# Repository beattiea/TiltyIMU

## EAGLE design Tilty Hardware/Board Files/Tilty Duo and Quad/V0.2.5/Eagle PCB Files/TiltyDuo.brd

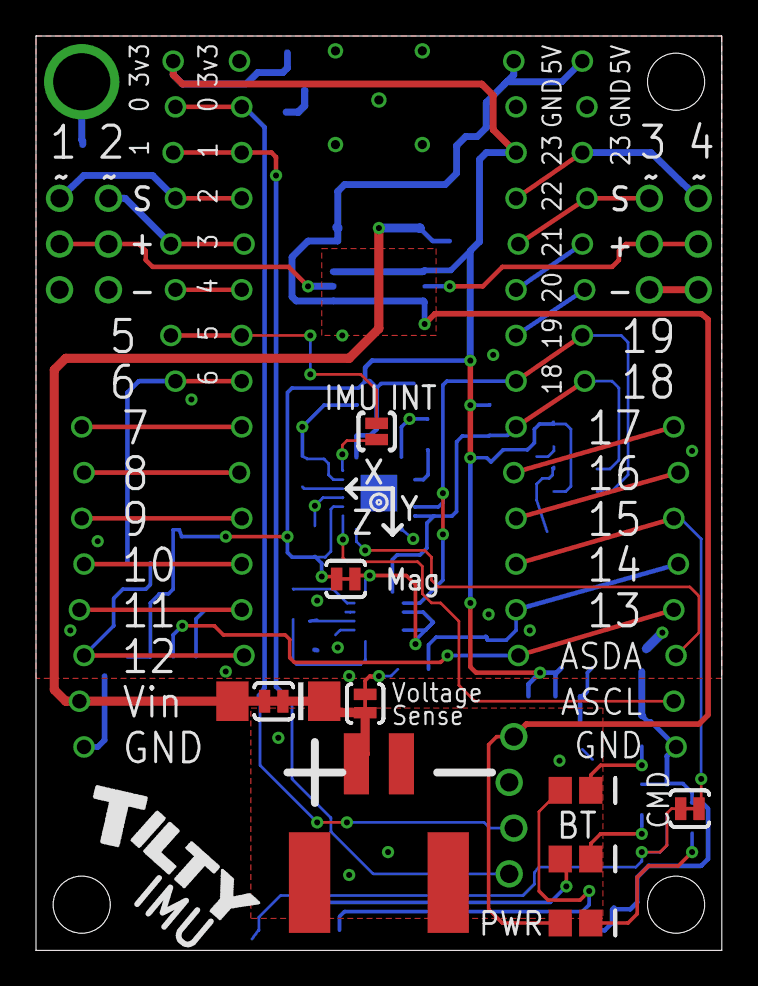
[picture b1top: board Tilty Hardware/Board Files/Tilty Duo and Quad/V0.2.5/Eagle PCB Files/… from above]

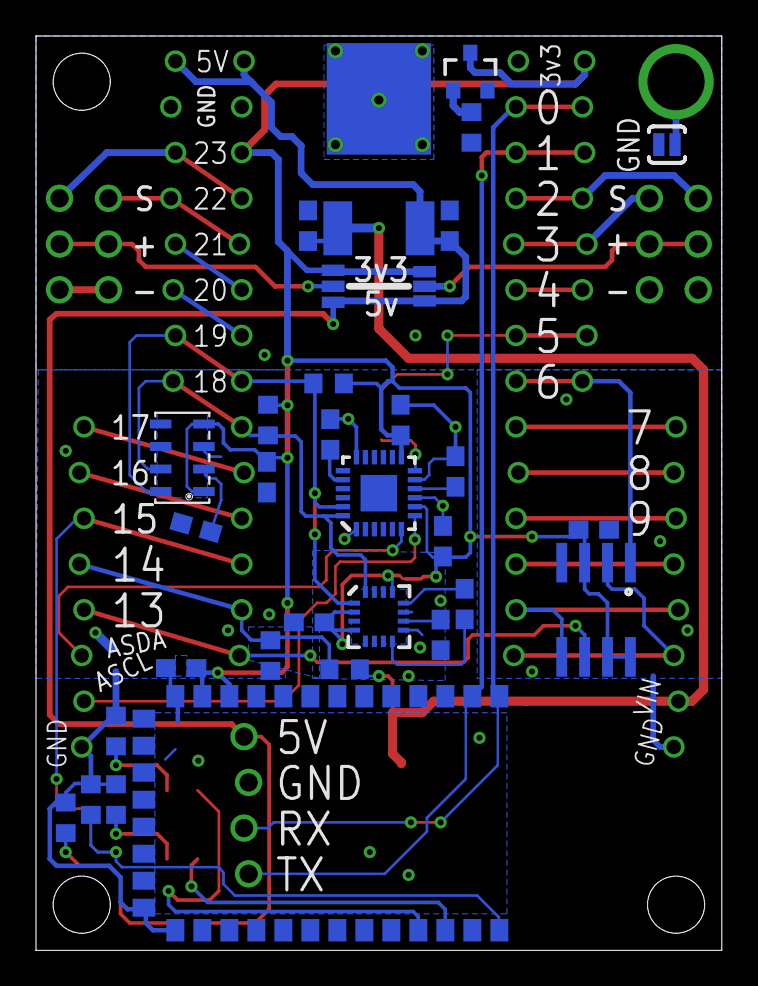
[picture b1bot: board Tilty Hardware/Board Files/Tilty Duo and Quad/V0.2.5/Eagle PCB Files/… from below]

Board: 2 copper layers, 38.1 x 50.8 mm, 50 parts (32 on the bottom side), 48 nets.

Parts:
C1, C2, C4, C6, C9, C10, C11, C12, C13: 0.1uF; C0603
C3: 2.2nF; C0603
C5, C8: 4.7uF; C0603
C7: 0.22uF; C0603
D1: RED; LED-0805
D2: GREEN; LED-0805
D3: YELLOW; LED-0805
D5: SOT23-3
D6: DO214AA
JP1, JP2, JP3, JP4: 8-PIN_HEADER; 8-PIN_RECEPTACLE_LOCK_NO-SS
JP5: 2-POS_SMD_TERM_BLOCK; 2-POS_SMD_TERMINAL_BLOCK
JP6, JP7: 2X03_NO_SS_LOCK
JP9: 1X04_NO_SS_LOCKING
MPU_INT: SOLDERJUMPERNO; SJ_2S-NO
R1, R2: 4.7K; R0603
R3: 180; R0603
R4, R8: 68; R0603
R5: 10k; R0603
R6: 680; R0603
R7: 10K; R0603
R9: R0603
SJ1: SOLDERJUMPERNO; SJ_2S-NO
SJ2: SJ_3_PASTE1&2
SJ3: SJ_3
SJ4, SJ5, SJ6, SJ7: SOLDERJUMPERTRACE; SJ_2S-TRACE
U1: TEENSY_3.0_OUTER-PINS28-DIP_SOCKET; 28-DIP
U2: MPU-6050; QFN-24
U3: LM2931; TO263
U4: SPI_FLASH-X25XXSMD; SO08
U5: HC-09_BREAKOUT
U6: HMC5883LSMD; 16LPCC
U7: MPL3115A2LGA8; LGA8

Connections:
5V: C5.1, D2.1, JP4.P$1, JP9.4, SJ2.1, SJ3.1, U1.P$15, U3.P$3
AUXCL: JP3.P$7, U2.7
AUXDA: JP3.P$6, U2.6
BATT_SENSE: JP3.P$4, R5.2, R6.2, U1.P$27
BT_CMD: JP3.P$3, SJ5.1, U1.P$26
CMD: R7.2, SJ5.2, U5.P$34
CS: JP1.P$1, U1.P$8, U4.1
GND: C1.2, C2.1, C3.2, C4.2, C5.2, C6.2, C8.2, C9.2, C10.2, C11.1, C12.1, C13.1, JP2.P$1, JP3.P$8, JP4.P$2, JP5.P$4, JP6.1, JP6.2, JP7.1, JP7.2, JP9.3, R3.1, R4.2, R6.1, R7.1, R8.1, R9.1, SJ1.2, U1.P$1, U1.P$16, U2.1, U2.9, U2.11, U2.18, U3.P$1, U4.4, U5.P$13, U5.P$21, U5.P$22, U6.9, U6.11, U7.3
I/O1: JP1.P$5, JP6.6, U1.P$4
I/O2: JP1.P$4, JP6.5, U1.P$5
I/O3: JP4.P$3, JP7.5, U1.P$18
I/O4: JP4.P$4, JP7.6, U1.P$19
MISO: JP2.P$3, U1.P$14, U4.2
MOSI: JP2.P$4, U1.P$13, U4.5
MPU_INT: JP1.P$2, MPU_INT.1, U1.P$7
unnamed: C1.1, U2.10
unnamed: C3.1, U2.20
unnamed: D1.2, R3.2
unnamed: C7.1, U6.8
unnamed: C7.2, U6.12
unnamed: JP1.P$3, U1.P$6
unnamed: JP2.P$5, U1.P$12
unnamed: R5.1, SJ4.2
unnamed: JP3.P$1, U1.P$24
unnamed: C8.1, U6.10
unnamed: JP2.P$6, U1.P$11
unnamed: D2.2, R4.1
unnamed: D1.1, U5.P$31
unnamed: MPU_INT.2, U2.12
unnamed: C6.1, SJ7.2, U6.2, U6.4, U6.13
unnamed: JP4.P$5, U1.P$20
unnamed: JP4.P$6, U1.P$21
unnamed: C10.1, U7.2
unnamed: D5.1, R9.2
unnamed: JP3.P$2, U1.P$25
unnamed: D3.2, R8.2
POW_I/O1: JP6.3, JP6.4, SJ2.2
POW_I/O2: JP7.3, JP7.4, SJ3.2
RX1: JP1.P$7, JP9.2, U1.P$2, U5.P$1
RX3: JP2.P$8, U1.P$9
SCK: JP3.P$5, U1.P$28, U4.6
SCL: JP4.P$7, R1.1, U1.P$22, U2.23, U6.1, U7.8
SDA: JP4.P$8, R2.1, U1.P$23, U2.24, U6.16, U7.7
TEENSY_3V3: C2.2, C9.1, C11.2, C12.2, C13.2, D5.3, JP1.P$8, R1.2, R2.2, SJ2.3, SJ3.3, SJ7.1, U1.P$17, U2.8, U2.13, U4.3, U4.7, U4.8, U5.P$11, U5.P$12, U7.1, U7.4
TX1: JP1.P$6, JP9.1, U1.P$3, U5.P$2
TX3: JP2.P$7, U1.P$10
VBATT: C4.1, D6.A, D6.C, JP2.P$2, JP5.P$3, SJ4.1, SJ6.1, SJ6.2, U3.P$2
YEL_LED: D3.1, U5.P$32

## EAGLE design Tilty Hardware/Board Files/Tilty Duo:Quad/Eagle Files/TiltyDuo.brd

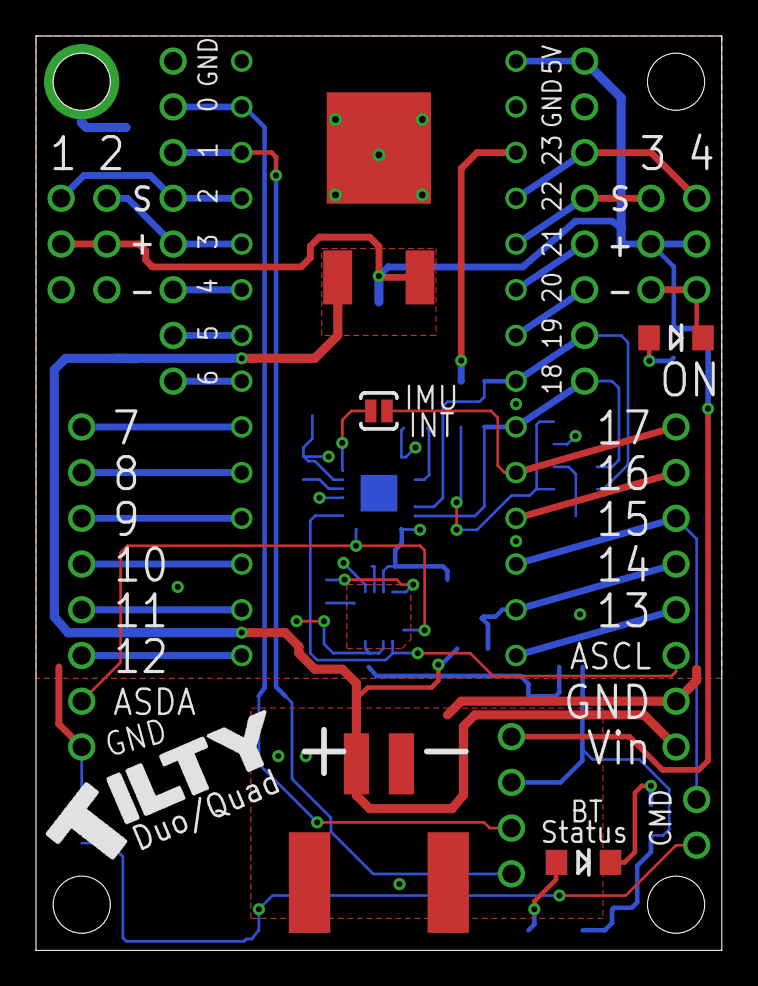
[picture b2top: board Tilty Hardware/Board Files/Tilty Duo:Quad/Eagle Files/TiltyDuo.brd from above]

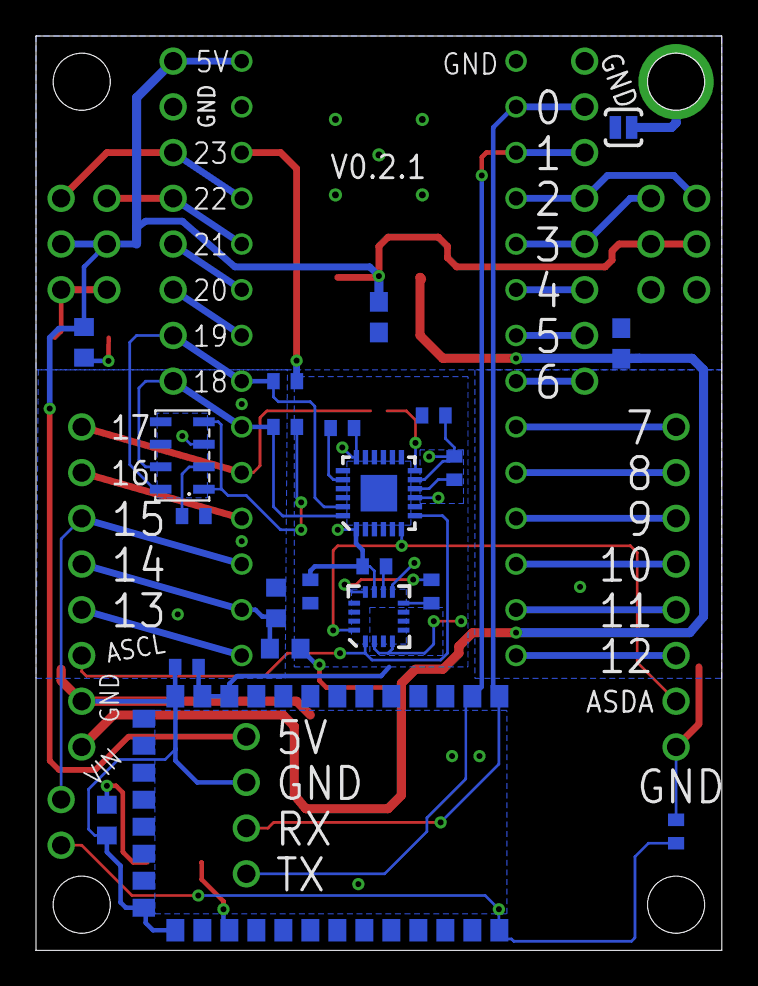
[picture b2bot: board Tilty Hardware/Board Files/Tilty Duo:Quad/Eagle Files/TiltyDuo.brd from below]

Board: 2 copper layers, 38.1 x 50.8 mm, 36 parts (22 on the bottom side), 41 nets.

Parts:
C1, C2, C6, C9, C10: 0.1uF; C0402
C3: 2.2nF; C0402
C4: 0.1uF; C0603
C5: 1uF; C0603
C7: 0.22uF; C0402
C8: 4.7uF; C0402
D1: GREEN; LED-1206_NO_SS
D2: RED; LED-1206_NO_SS
JP1, JP2, JP5, JP6: 1X08_NO_SS
JP3, JP7: 2X03_NO_SS
JP4: 2-POS_SMD_TERM_BLOCK; 2-POS_SMD_TERMINAL_BLOCK
JP8: 1X02_NO_SS
JP9: 1X04
MPU_INT: SOLDERJUMPERNO; SJ_2S-NO
R1, R2, R7: 4.7K; R0402
R3: 470; R0603
R4: 180; R0603
R5: 10k; R0603
R6: 680; R0603
SJ1: SOLDERJUMPERNO; SJ_2S-NO
U1: TEENSY_3.0_OUTER-PINS28-DIP_SOCKET; 28-DIP
U2: HC-09_BREAKOUT
U3: MPL3115A2LGA8; LGA8
U4: LM2931; TO263
U5: MPU-6050; QFN-24
U6: HMC5883LSMD; 16LPCC

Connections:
5V: C5.1, JP3.3, JP3.4, JP5.8, JP7.3, JP7.4, JP9.4, R4.1, U1.P$15, U4.P$3
AUXCL: JP6.3, U5.7, U6.1
AUXDA: JP2.2, U5.6, U6.16
BATT_SENSE: JP6.5, R5.2, R6.2, U1.P$27
BT_CMD: JP6.6, JP8.1, U1.P$26
CMD: JP8.2, R7.2, U2.P$34
GND: C1.2, C2.1, C3.2, C4.2, C5.2, C6.2, C8.2, C9.2, C10.2, D2.C, JP1.8, JP2.1, JP3.1, JP3.2, JP4.P$4, JP5.7, JP6.2, JP7.1, JP7.2, JP9.3, R3.1, R6.1, R7.1, SJ1.2, U1.P$1, U2.P$13, U2.P$21, U2.P$22, U3.3, U4.P$1, U5.1, U5.9, U5.11, U5.18, U6.9, U6.11
I/O1: JP1.5, JP3.6, U1.P$4
I/O2: JP1.4, JP3.5, U1.P$5
I/O3: JP5.6, JP7.5, U1.P$18
I/O4: JP5.5, JP7.6, U1.P$19
LED: D1.A, U2.P$24
MPU_INT: JP6.8, MPU_INT.1, U1.P$24
unnamed: C1.1, U5.10
unnamed: C3.1, U5.20
unnamed: D1.C, R3.2
unnamed: C7.1, U6.8
unnamed: C7.2, U6.12
unnamed: JP1.3, U1.P$6
unnamed: JP1.2, U1.P$7
unnamed: JP1.1, U1.P$8
unnamed: JP6.4, U1.P$28
unnamed: C8.1, U6.10
unnamed: JP2.6, U1.P$11
unnamed: JP2.5, U1.P$12
unnamed: JP2.4, U1.P$13
unnamed: JP2.3, U1.P$14
unnamed: MPU_INT.2, U5.12
unnamed: D2.A, R4.2
unnamed: JP5.4, U1.P$20
unnamed: JP5.3, U1.P$21
unnamed: C10.1, U3.2
unnamed: JP6.7, U1.P$25
RX1: JP1.7, JP9.2, U1.P$2, U2.P$1
RX3: JP2.8, U1.P$9
SCL: JP5.2, R1.1, U1.P$22, U3.8, U5.23
SDA: JP5.1, R2.1, U1.P$23, U3.7, U5.24
TEENSY_3V3: C2.2, C6.1, C9.1, R1.2, R2.2, U1.P$17, U2.P$11, U2.P$12, U3.1, U3.4, U5.8, U5.13, U6.2, U6.4, U6.13
TX1: JP1.6, JP9.1, U1.P$3, U2.P$2
TX3: JP2.7, U1.P$10
VBATT: C4.1, JP4.P$3, JP6.1, R5.1, U4.P$2

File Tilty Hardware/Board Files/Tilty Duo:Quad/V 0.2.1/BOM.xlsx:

Part | Package | Name | Quantity | Supplier 1 | Part # 1 | Cost per 1 | Cost per 10 | Cost per 25 | Cost per 50 | Cost per 100 | Supplier 2 | Part # 2 | Cost | Quantity |  | Cost/board for 50 boards
Teensy DIP Socket | DIP | U1 | 1 | Digikey | AE10004-ND | 0.42 | 0.39900000000000002 | 0.34200000000000003 | 0.2908 | 0.27929999999999999 | Avnet | 1-390262-2 | 0.22320000000000001 | 50 |  | 0.2908
Bluetooth Module | Surface mount | U2 | 1 | Aliexpress |  | 5.99 | 5.99 | 4.12 | 4.12 | 4.0999999999999996 | eBay |  |  |  |  | 4.12
Voltage Regulator | Dpak | U4 | 1 | Digikey | LM2931ADT-5.0GOS-ND | 0.78 | 0.78 | 0.60599999999999998 | 0.60599999999999998 | 0.52790000000000004 | Avnet | LM2931DT-5.0G | 0.375 | 1 |  | 0.60599999999999998
MPU-6050 IMU | QFN | U5 | 1 | Aliexpress |  | 4 | 2.5 | 2.5 | 2.5 | 2.5 | eBay |  |  |  |  | 2.5
1x8 Female headers | DIP | JP1, JP2, JP5, JP6 | 4 | Aliexpress |  | 1.43 | 1.2989999999999999 | 1.2989999999999999 | 1.1659999999999999 | 0.16 | Digikey | 535541-6 |  |  |  | 4.6639999999999997
2x40 Male Headers (cut from strip) | DIP | JP3, JP7, JP8 | 0.2 | Aliexpress |  | 1.03 | 0.91800000000000004 | 0.91800000000000004 | 0.91800000000000004 | 0.12 | Digikey | S2012EC-40-ND |  |  |  | 0.18360000000000001
Power Terminal | Surface mount | JP4 | 1 | Digikey | 277-2337-1-ND | 0.61 | 0.56399999999999995 | 0.56399999999999995 | 0.54059999999999997 | 0.51700000000000002 |  |  |  |  |  | 0.54059999999999997
Green LED | 1206 | D1 | 1 | Digikey | L71504CT-ND | 0.5 | 0.38900000000000001 | 0.31680000000000003 | 0.31680000000000003 | 0.252 | Check Avne for alternative |  |  |  |  | 0.31680000000000003
Red LED | 1206 | D2 | 1 | Digikey | 516-2825-1-ND | 0.56000000000000005 | 0.43 | 0.36 | 0.36 | 0.31 | Check Avne for alternative |  |  |  |  | 0.36
4.7K Ω Resistor | 0402 | R1, R2, R7 | 3 | Digikey | P4.7KJCT-ND | 0.1 | 0.1 | 0.1 | 1.72E-2 | 1.3100000000000001E-2 | Avnet | ERJ-2GEJ472X | 2E-3 | 10000 |  | 5.16E-2
470 Ω Resistor | 0603 | R3 | 1 | Digikey | RMCF0603JT470RCT-ND | 0.02 | 1.7000000000000001E-2 | 1.7000000000000001E-2 | 9.1999999999999998E-3 | 7.0000000000000001E-3 | Avnet | RMCF0603JT470R | 1.6000000000000001E-3 | 5000 |  | 9.1999999999999998E-3
180 Ω Resistor | 0603 | R4 | 1 | Digikey | RNCP0603FTD180RCT-ND | 0.05 | 3.7999999999999999E-2 | 3.7999999999999999E-2 | 2.0799999999999999E-2 | 1.5800000000000002E-2 | Avnet | ERJ-3GEYJ181V | 1.1000000000000001E-3 | 5000 |  | 2.0799999999999999E-2
10K Ω Resistor | 0603 | R5 | 1 | Digikey | RMCF0603JT10K0CT-ND | 0.02 | 1.7000000000000001E-2 | 1.7000000000000001E-2 | 9.1999999999999998E-3 | 7.0000000000000001E-3 | Avnet | RMCF0603JT10K0 | 1.6000000000000001E-3 | 5000 |  | 9.1999999999999998E-3
680 Ω Resistor | 0603 | R6 | 1 | Digikey | RMCF0603JT680R | 0.02 | 1.7000000000000001E-2 | 1.7000000000000001E-2 | 9.1999999999999998E-3 | 7.0000000000000001E-3 | Avnet | RMCF0603JT680R | 1.6000000000000001E-3 | 5000 |  | 9.1999999999999998E-3
0.1 µF Capacitor | 0402 | C1, C2, C9 | 3 | Digikey | C1005X5R1A104K050BA | 0.1 | 2.5000000000000001E-2 | 2.5000000000000001E-2 | 2.5000000000000001E-2 | 1.1599999999999999E-2 | Avnet | C1005X5R1A104K050BA | 3.7000000000000002E-3 | 10000 |  | 7.5000000000000011E-2
2.2 nF Capacitor | 0402 | C3 | 1 | Digikey | C1005X7R1H222K050BA | 0.1 | 2.4E-2 | 2.4E-2 | 2.4E-2 | 1.0999999999999999E-2 | Avnet | C1005X7R1H222K050BA | 3.5000000000000001E-3 | 10000 |  | 2.4E-2
0.1 µF Capacitor | 0603 | C4 | 1 | Digikey | C1608Y5V1H104Z | 0.1 | 2.8000000000000001E-2 | 2.8000000000000001E-2 | 2.8000000000000001E-2 | 1.26E-2 | Avnet | C1608Y5V1H104Z | 3.8999999999999998E-3 | 4000 |  | 2.8000000000000001E-2
1 µF Capacitor | 0603 | C5 | 1 | Digikey | C1608X5R1A105K080AC | 0.1 | 6.2E-2 | 6.2E-2 | 6.2E-2 | 2.86E-2 | Avnet | C1608X5R1A105K080AC | 9.1999999999999998E-3 | 4000 |  | 6.2E-2
 |  |  |  |  |  |  |  |  |  |  |  |  |  |  |  | 13.870799999999997

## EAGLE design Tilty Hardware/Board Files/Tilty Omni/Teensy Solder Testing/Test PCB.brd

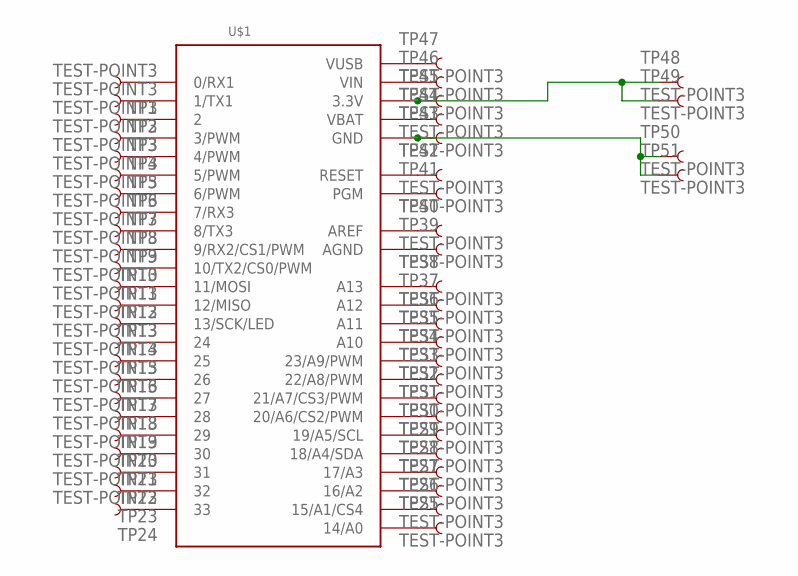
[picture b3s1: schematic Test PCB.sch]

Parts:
TP1, TP2, TP3, TP4, TP5, TP6, TP7, TP8, TP9, TP10, TP11, TP12, TP13, TP14, TP15, TP16, TP17, TP18, TP19, TP20, TP21, TP22, TP23, TP24, TP25, TP26, TP27, TP28, TP29, TP30, TP31, TP32, TP33, TP34, TP35, TP36, TP37, TP38, TP39, TP40, TP41, TP42, TP43, TP44, TP45, TP46, TP47, TP48, TP49, TP50, TP51: TEST-POINT3; PAD.03X.03
U$1: TEENSY_3.0_ALLPINSTEENSY_3.0_ALLPINS-SMD; TEENSY_3.0_ALLPINS-SMD

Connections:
unnamed: TP1.P$1, U$1.0 (0/RX1)
unnamed: TP2.P$1, U$1.1 (1/TX1)
unnamed: TP3.P$1, U$1.2
unnamed: TP4.P$1, U$1.3 (3/PWM)
unnamed: TP5.P$1, U$1.4 (4/PWM)
unnamed: TP6.P$1, U$1.5 (5/PWM)
unnamed: TP7.P$1, U$1.6 (6/PWM)
unnamed: TP8.P$1, U$1.7 (7/RX3)
unnamed: TP9.P$1, U$1.8 (8/TX3)
unnamed: TP10.P$1, U$1.9 (9/RX2/CS1/PWM)
unnamed: TP11.P$1, U$1.10 (10/TX2/CS0/PWM)
unnamed: TP12.P$1, U$1.11 (11/MOSI)
unnamed: TP13.P$1, U$1.12 (12/MISO)
unnamed: TP14.P$1, U$1.13 (13/SCK/LED)
unnamed: TP15.P$1, U$1.24
unnamed: TP16.P$1, U$1.25
unnamed: TP17.P$1, U$1.26
unnamed: TP18.P$1, U$1.27
unnamed: TP19.P$1, U$1.28
unnamed: TP20.P$1, U$1.29
unnamed: TP21.P$1, U$1.30
unnamed: TP22.P$1, U$1.31
unnamed: TP23.P$1, U$1.32
unnamed: TP24.P$1, U$1.33
unnamed: TP25.P$1, U$1.14/A0
unnamed: TP26.P$1, U$1.15/A1 (15/A1/CS4)
unnamed: TP27.P$1, U$1.16/A2
unnamed: TP28.P$1, U$1.17/A3
unnamed: TP29.P$1, U$1.18/A4 (18/A4/SDA)
unnamed: TP30.P$1, U$1.19/A5 (19/A5/SCL)
unnamed: TP31.P$1, U$1.20/A6 (20/A6/CS2/PWM)
unnamed: TP32.P$1, U$1.21/A7 (21/A7/CS3/PWM)
unnamed: TP33.P$1, U$1.22/A8 (22/A8/PWM)
unnamed: TP34.P$1, U$1.23/A9 (23/A9/PWM)
unnamed: TP35.P$1, U$1.A10
unnamed: TP36.P$1, U$1.A11
unnamed: TP37.P$1, U$1.A12
unnamed: TP38.P$1, U$1.A13
unnamed: TP39.P$1, U$1.AGND
unnamed: TP40.P$1, U$1.AREF
unnamed: TP41.P$1, U$1.PGM
unnamed: TP42.P$1, U$1.RESET
unnamed: TP44.P$1, U$1.VBAT
unnamed: TP43.P$1, TP50.P$1, TP51.P$1, U$1.GND, U$1.GND1 (GND), U$1.GND2 (GND)
unnamed: TP46.P$1, U$1.VIN
unnamed: TP47.P$1, U$1.VUSB
unnamed: TP45.P$1, TP48.P$1, TP49.P$1, U$1.3.3V, U$1.3.3V1 (3.3V), U$1.3.3V2 (3.3V)

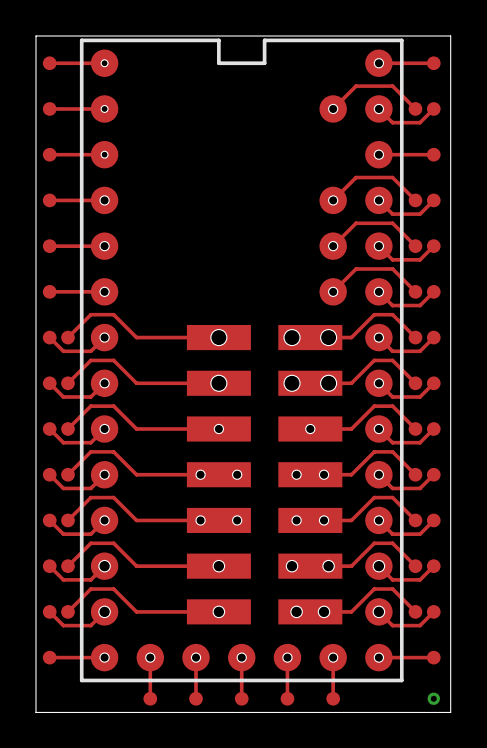
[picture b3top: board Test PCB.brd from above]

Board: 2 copper layers, 23.0 x 37.6 mm, 52 parts (0 on the bottom side), 47 nets.

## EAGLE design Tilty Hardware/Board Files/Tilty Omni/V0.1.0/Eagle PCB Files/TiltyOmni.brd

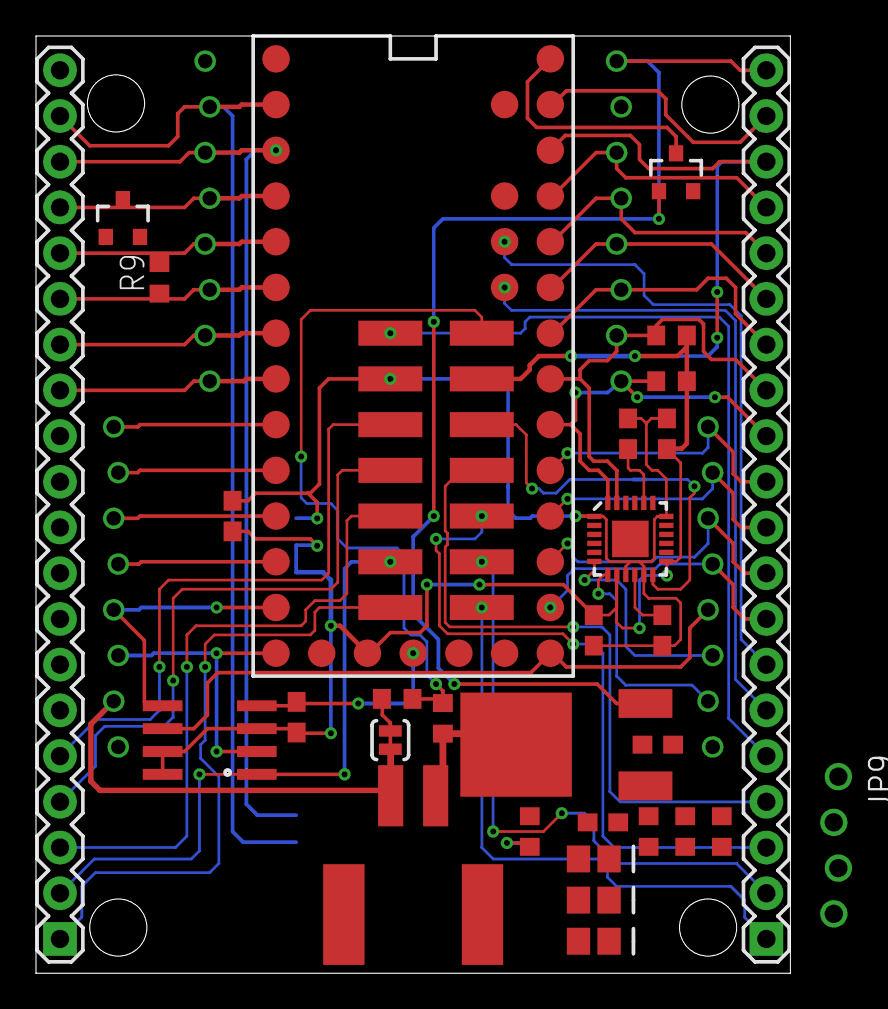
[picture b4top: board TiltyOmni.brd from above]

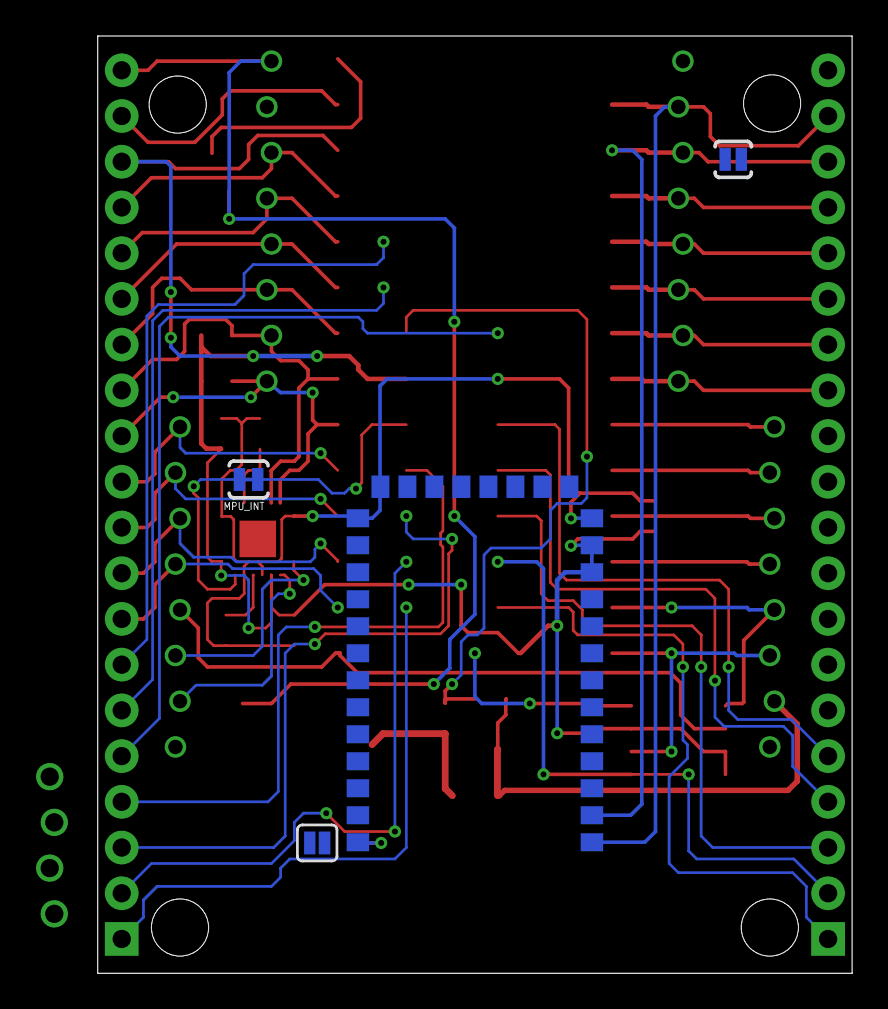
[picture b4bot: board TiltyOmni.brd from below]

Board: 2 copper layers, 41.9 x 52.1 mm, 39 parts (4 on the bottom side), 57 nets.

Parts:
C1, C2, C4, C9, C11, C13: 0.1uF; C0603
C3: 2.2nF; C0603
C5: 4.7uF; C0603
D1: RED; LED-0805
D2: GREEN; LED-0805
D3: YELLOW; LED-0805
D4, D5: SOT23-3
JP1, JP2, JP3, JP4: 8-PIN_HEADER; 8-PIN_RECEPTACLE_LOCK_NO-SS
JP5: 2-POS_SMD_TERM_BLOCK; 2-POS_SMD_TERMINAL_BLOCK
JP6, JP7: M20; 1X20
JP9: 1X04_NO_SS_LOCKING
MPU_INT: SOLDERJUMPERTRACE; SJ_2S-TRACE
R1, R2: 4.7K; R0603
R3: 180; R0603
R4, R8: 68; R0603
R5: 10k; R0603
R6: 680; R0603
R7: 10K; R0603
R9: R0603
SJ1: SOLDERJUMPERNO; SJ_2S-NO
SJ4: SOLDERJUMPERTRACE; SJ_2S-TRACE
SJ5: SJ_2S
U1: TEENSY_3.0_ALLPINSTEENSY_3.0_ALLPINS-SMD; TEENSY_3.0_ALLPINS-SMD
U2: HC-09_BREAKOUT
U4: LM2931; TO263
U5: MPU-6050; QFN-24
U7: SPI_FLASH-X25XXSMD; SO08

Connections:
3V_SCL: JP4.P$7, JP7.13, R1.1, U1.19/A5, U5.23
3V_SDA: JP4.P$8, JP7.12, R2.1, U1.18/A4, U5.24
4/PWM: JP1.P$6, JP6.15, U1.4
5/PWM: JP1.P$7, JP6.14, U1.5
5V_SCL: JP3.P$2, JP7.10, U1.16/A2
5V_SDA: JP3.P$1, JP7.11, U1.17/A3
6/PWM: JP1.P$8, JP6.13, U1.6
7/RX3: JP2.P$1, JP6.12, U1.7
8/TX3: JP2.P$2, JP6.11, U1.8
9/RX2: JP2.P$3, JP6.10, U1.9
10/TX2: JP2.P$4, JP6.9, U1.10
14/A0: JP3.P$4, JP7.8, U1.14/A0
15/A1: JP3.P$3, JP7.9, U1.15/A1
20/A6: JP4.P$6, JP7.14, U1.20/A6
21/A7: JP4.P$5, JP7.15, U1.21/A7
24: JP6.5, U1.24
25: JP6.4, U1.25
26: JP6.3, U1.26
29: JP7.1, U1.29
30: JP7.2, U1.30
31: JP7.3, U1.31
32: JP7.4, U1.32
+3V3: C2.2, C9.1, C11.2, C13.2, D5.3, JP1.P$1, JP7.18, R1.2, R2.2, U1.3.3V, U1.3.3V1, U1.3.3V2, U2.P$11, U2.P$12, U5.8, U5.13, U7.3, U7.7, U7.8
+5V: C5.1, D2.1, D4.1, JP4.P$1, JP7.20, JP9.4, U4.P$3
A10: JP7.7, U1.A10
A11: JP7.6, U1.A11
A12: JP7.5, U1.A12
AGND: JP7.19, U1.AGND
AUXCL: JP3.P$7, U5.7
AUXDA: JP3.P$6, U5.6
BATT_SENSE: R5.2, R6.2, U1.A13
BLUETOOTH_RX: JP1.P$2, JP6.19, U1.0, U2.P$1
BLUETOOTH_TX: JP1.P$3, JP6.18, U1.1, U2.P$2
BT_CMD: JP6.1, SJ5.1, U1.28
CMD: R7.2, SJ5.2, U2.P$34
GND: C1.2, C2.1, C3.2, C4.2, C5.2, C9.2, C11.1, C13.1, JP2.P$8, JP3.P$8, JP4.P$2, JP5.P$4, JP6.20, JP9.3, R3.1, R4.2, R6.1, R7.1, R8.1, R9.1, SJ1.2, U1.GND, U1.GND1, U1.GND2, U2.P$13, U2.P$21, U2.P$22, U4.P$1, U5.1, U5.9, U5.11, U5.18, U7.4
IMU_INT: MPU_INT.1, U1.33
MEMORY_CS: JP6.2, U1.27, U7.1
MISO: JP2.P$6, JP6.7, U1.12, U7.2
MOSI: JP2.P$5, JP6.8, U1.11, U7.5
unnamed: C1.1, U5.10
unnamed: C3.1, U5.20
unnamed: D1.2, R3.2
unnamed: D4.3, U1.VIN
unnamed: D5.1, R9.2
unnamed: R5.1, SJ4.2
unnamed: D2.2, R4.1
unnamed: D1.1, U2.P$31
unnamed: MPU_INT.2, U5.12
unnamed: D3.2, R8.2
SCK: JP3.P$5, JP6.6, U1.13, U7.6
SERVO_1: JP1.P$4, JP6.17, U1.2
SERVO_2: JP1.P$5, JP6.16, U1.3
SERVO_3: JP4.P$4, JP7.16, U1.22/A8
SERVO_4: JP4.P$3, JP7.17, U1.23/A9
VCC: C4.1, JP2.P$7, JP5.P$3, SJ4.1, U4.P$2
YEL_LED: D3.1, U2.P$32

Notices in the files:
parts and their libraries:
SparkFun-Sensors: Licensing: CC v3.0 Share-Alike You are welcome to use this library for commercial purposes.
